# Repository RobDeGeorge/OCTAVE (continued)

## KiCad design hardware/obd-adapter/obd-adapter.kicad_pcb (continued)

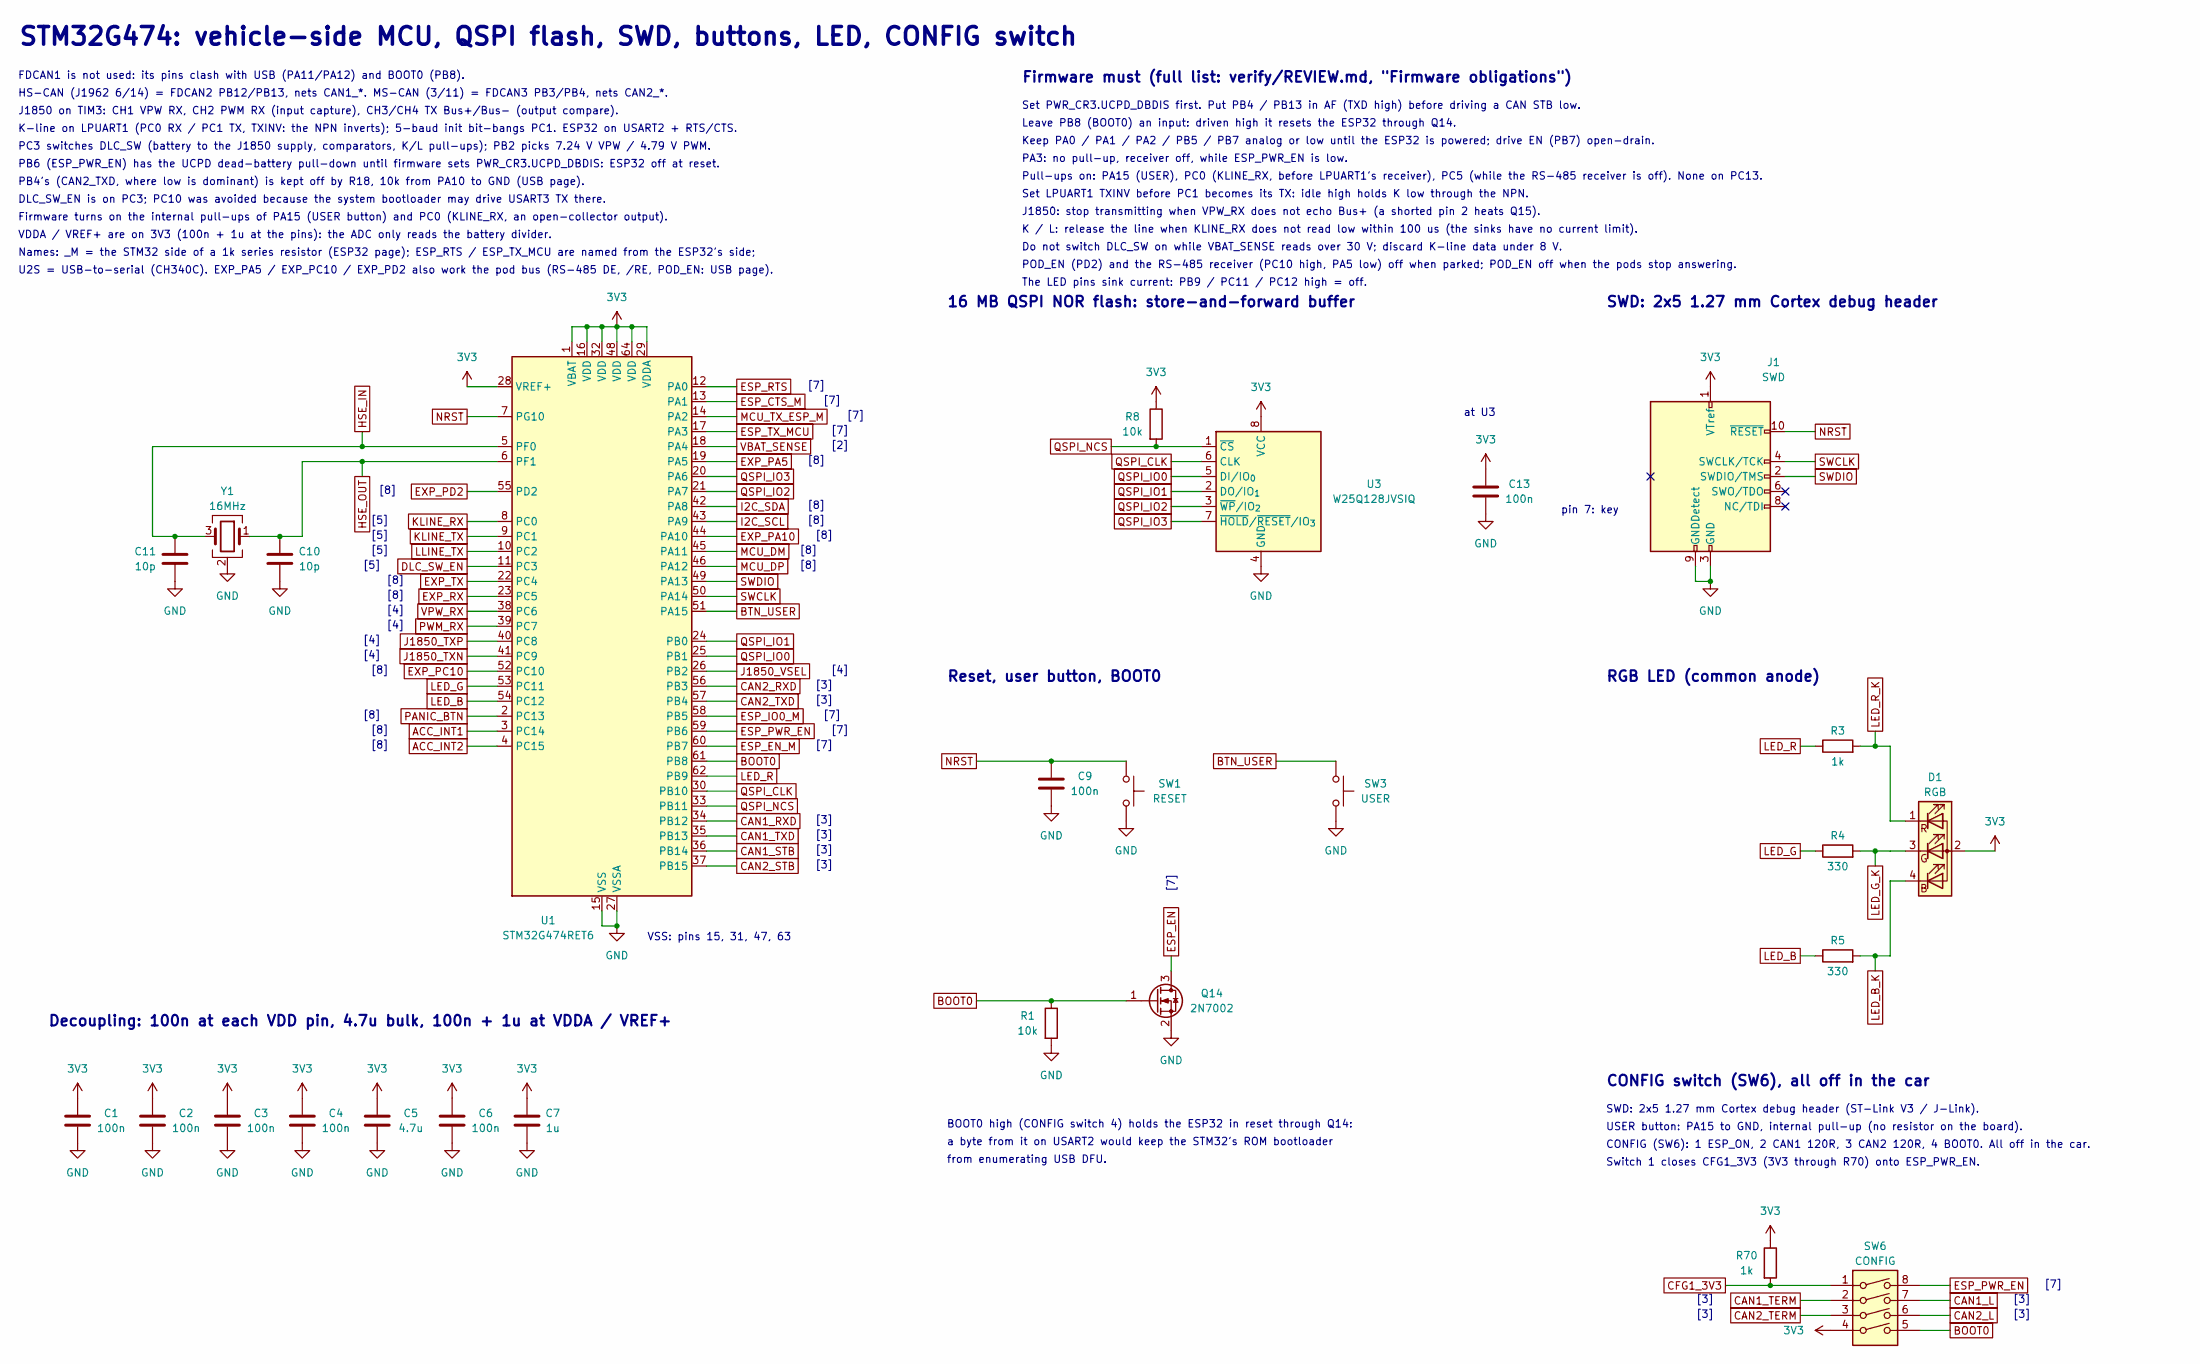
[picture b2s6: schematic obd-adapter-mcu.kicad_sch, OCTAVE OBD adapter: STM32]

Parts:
C1, C2, C3, C4, C6, C9, C13: 100n; C_0402_1005Metric; LCSC C307331
C5: 4.7u; C_0603_1608Metric; LCSC C19666
C7: 1u; C_0402_1005Metric; LCSC C52923
C10, C11: 10p; C_0402_1005Metric; LCSC C32949
D1: RGB; LED_RGB_1615; LCSC C965840
J1: SWD; PinHeader_2x05_P1.27mm_Vertical_SMD; LCSC C41376037
Q14: 2N7002; SOT-23; LCSC C8545
R1, R8: 10k; R_0402_1005Metric; LCSC C25744
R3, R70: 1k; R_0402_1005Metric; LCSC C11702
R4, R5: 330; R_0402_1005Metric; LCSC C25104
SW1: RESET; SW_Push_1P1T_XKB_TS-1187A; LCSC C318884
SW3: USER; SW_Push_1P1T_XKB_TS-1187A; LCSC C318884
SW6: CONFIG; SW_DIP_SPSTx04_Slide_KingTek_DSHP04TS_W7.62mm_P1.27mm; LCSC C40736
U1: STM32G474RET6; LQFP-64_10x10mm_P0.5mm; LCSC C521608
U3: W25Q128JVSIQ; SOIC-8_5.3x5.3mm_P1.27mm; LCSC C97521
Y1: 16MHz; Crystal_SMD_3225-4Pin_3.2x2.5mm; LCSC C13738

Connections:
3V3: C1.1, C2.1, C3.1, C4.1, C5.1, C6.1, C7.1, C13.1, D1.2 (A), J1.1 (VTref), R8.1, R70.1, SW6.4, U1.1 (VBAT), U1.16 (VDD), U1.28 (VREF+), U1.29 (VDDA), U1.32 (VDD), U1.48 (VDD), U1.64 (VDD), U3.8 (VCC); also elsewhere on the board
ACC_INT1: U1.3 (PC14); also elsewhere on the board
ACC_INT2: U1.4 (PC15); also elsewhere on the board
BOOT0: Q14.1 (G), R1.1, SW6.5, U1.61 (PB8)
BTN_USER: SW3.1, U1.51 (PA15)
CAN1_L: SW6.7; also elsewhere on the board
CAN1_RXD: U1.34 (PB12); also elsewhere on the board
CAN1_STB: U1.36 (PB14); also elsewhere on the board
CAN1_TERM: SW6.2; also elsewhere on the board
CAN1_TXD: U1.35 (PB13); also elsewhere on the board
CAN2_L: SW6.6; also elsewhere on the board
CAN2_RXD: U1.56 (PB3); also elsewhere on the board
CAN2_STB: U1.37 (PB15); also elsewhere on the board
CAN2_TERM: SW6.3; also elsewhere on the board
CAN2_TXD: U1.57 (PB4); also elsewhere on the board
CFG1_3V3: R70.2, SW6.1
DLC_SW_EN: U1.11 (PC3); also elsewhere on the board
ESP_CTS_M: U1.13 (PA1); also elsewhere on the board
ESP_EN: Q14.3 (D); also elsewhere on the board
ESP_EN_M: U1.60 (PB7); also elsewhere on the board
ESP_IO0_M: U1.58 (PB5); also elsewhere on the board
ESP_PWR_EN: SW6.8, U1.59 (PB6); also elsewhere on the board
ESP_RTS: U1.12 (PA0); also elsewhere on the board
ESP_TX_MCU: U1.17 (PA3); also elsewhere on the board
EXP_PA5: U1.19 (PA5); also elsewhere on the board
EXP_PA10: U1.44 (PA10); also elsewhere on the board
EXP_PC10: U1.52 (PC10); also elsewhere on the board
EXP_PD2: U1.55 (PD2); also elsewhere on the board
EXP_RX: U1.23 (PC5); also elsewhere on the board
EXP_TX: U1.22 (PC4); also elsewhere on the board
GND: C1.2, C2.2, C3.2, C4.2, C5.2, C6.2, C7.2, C9.2, C10.2, C11.2, C13.2, J1.3 (GND), J1.5 (GND), J1.9 (GNDDetect), Q14.2 (S), R1.2, SW1.2, SW3.2, U1.15 (VSS), U1.27 (VSSA), U1.31 (VSS), U1.47 (VSS), U1.63 (VSS), U3.4 (GND), Y1.2 (G), Y1.4 (G); also elsewhere on the board
HSE_IN: C11.1, U1.5 (PF0), Y1.3
HSE_OUT: C10.1, U1.6 (PF1), Y1.1
I2C_SCL: U1.43 (PA9); also elsewhere on the board
I2C_SDA: U1.42 (PA8); also elsewhere on the board
J1850_TXN: U1.41 (PC9); also elsewhere on the board
J1850_TXP: U1.40 (PC8); also elsewhere on the board
J1850_VSEL: U1.26 (PB2); also elsewhere on the board
KLINE_RX: U1.8 (PC0); also elsewhere on the board
KLINE_TX: U1.9 (PC1); also elsewhere on the board
LED_B: R5.1, U1.54 (PC12)
LED_B_K: D1.4 (BK), R5.2
LED_G: R4.1, U1.53 (PC11)
LED_G_K: D1.3 (GK), R4.2
LED_R: R3.1, U1.62 (PB9)
LED_R_K: D1.1 (RK), R3.2
LLINE_TX: U1.10 (PC2); also elsewhere on the board
MCU_DM: U1.45 (PA11); also elsewhere on the board
MCU_DP: U1.46 (PA12); also elsewhere on the board
MCU_TX_ESP_M: U1.14 (PA2); also elsewhere on the board
NRST: C9.1, J1.10 (~RESET), SW1.1, U1.7 (PG10)
PANIC_BTN: U1.2 (PC13); also elsewhere on the board
PWM_RX: U1.39 (PC7); also elsewhere on the board
QSPI_CLK: U1.30 (PB10), U3.6 (CLK)
QSPI_IO0: U1.25 (PB1), U3.5 (DI/IO_{0})
QSPI_IO1: U1.24 (PB0), U3.2 (DO/IO_{1})
QSPI_IO2: U1.21 (PA7), U3.3 (~WP/IO_{2})
QSPI_IO3: U1.20 (PA6), U3.7 (~HOLD/~RESET/IO_{3})
QSPI_NCS: R8.2, U1.33 (PB11), U3.1 (~CS)
SWCLK: J1.4 (SWCLK/TCK), U1.50 (PA14)
SWDIO: J1.2 (SWDIO/TMS), U1.49 (PA13)
VBAT_SENSE: U1.18 (PA4); also elsewhere on the board
VPW_RX: U1.38 (PC6); also elsewhere on the board

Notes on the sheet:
STM32G474: vehicle-side MCU, QSPI flash, SWD, buttons, LED, CONFIG switch
FDCAN1 is not used: its pins clash with USB (PA11/PA12) and BOOT0 (PB8).
HS-CAN (J1962 6/14) = FDCAN2 PB12/PB13, nets CAN1_*. MS-CAN (3/11) = FDCAN3 PB3/PB4, nets CAN2_*.
J1850 on TIM3: CH1 VPW RX, CH2 PWM RX (input capture), CH3/CH4 TX Bus+/Bus- (output compare).
K-line on LPUART1 (PC0 RX / PC1 TX, TXINV: the NPN inverts); 5-baud init bit-bangs PC1. ESP32 on USART2 + RTS/CTS.
PC3 switches DLC_SW (battery to the J1850 supply, comparators, K/L pull-ups); PB2 picks 7.24 V VPW / 4.79 V PWM.
PB6 (ESP_PWR_EN) has the UCPD dead-battery pull-down until firmware sets PWR_CR3.UCPD_DBDIS: ESP32 off at reset.
PB4's (CAN2_TXD, where low is dominant) is kept off by R18, 10k from PA10 to GND (USB page).
DLC_SW_EN is on PC3; PC10 was avoided because the system bootloader may drive USART3 TX there.
Firmware turns on the internal pull-ups of PA15 (USER button) and PC0 (KLINE_RX, an open-collector output).
VDDA / VREF+ are on 3V3 (100n + 1u at the pins): the ADC only reads the battery divider.
Names: _M = the STM32 side of a 1k series resistor (ESP32 page); ESP_RTS / ESP_TX_MCU are named from the ESP32's side;
U2S = USB-to-serial (CH340C). EXP_PA5 / EXP_PC10 / EXP_PD2 also work the pod bus (RS-485 DE, /RE, POD_EN: USB page).
Firmware must (full list: verify/REVIEW.md, "Firmware obligations")
Set PWR_CR3.UCPD_DBDIS first. Put PB4 / PB13 in AF (TXD high) before driving a CAN STB low.
Leave PB8 (BOOT0) an input: driven high it resets the ESP32 through Q14.
Keep PA0 / PA1 / PA2 / PB5 / PB7 analog or low until the ESP32 is powered; drive EN (PB7) open-drain.
PA3: no pull-up, receiver off, while ESP_PWR_EN is low.
Pull-ups on: PA15 (USER), PC0 (KLINE_RX, before LPUART1's receiver), PC5 (while the RS-485 receiver is off). None on PC13.
Set LPUART1 TXINV before PC1 becomes its TX: idle high holds K low through the NPN.
J1850: stop transmitting when VPW_RX does not echo Bus+ (a shorted pin 2 heats Q15).
K / L: release the line when KLINE_RX does not read low within 100 us (the sinks have no current limit).
Do not switch DLC_SW on while VBAT_SENSE reads over 30 V; discard K-line data under 8 V.
POD_EN (PD2) and the RS-485 receiver (PC10 high, PA5 low) off when parked; POD_EN off when the pods stop answering.
The LED pins sink current: PB9 / PC11 / PC12 high = off.
VSS: pins 15, 31, 47, 63
Decoupling: 100n at each VDD pin, 4.7u bulk, 100n + 1u at VDDA / VREF+
16 MB QSPI NOR flash: store-and-forward buffer
at U3
Reset, user button, BOOT0
BOOT0 high (CONFIG switch 4) holds the ESP32 in reset through Q14:
a byte from it on USART2 would keep the STM32's ROM bootloader
from enumerating USB DFU.
SWD: 2x5 1.27 mm Cortex debug header
pin 7: key
RGB LED (common anode)
CONFIG switch (SW6), all off in the car
SWD: 2x5 1.27 mm Cortex debug header (ST-Link V3 / J-Link).
USER button: PA15 to GND, internal pull-up (no resistor on the board).
CONFIG (SW6): 1 ESP_ON, 2 CAN1 120R, 3 CAN2 120R, 4 BOOT0. All off in the car.

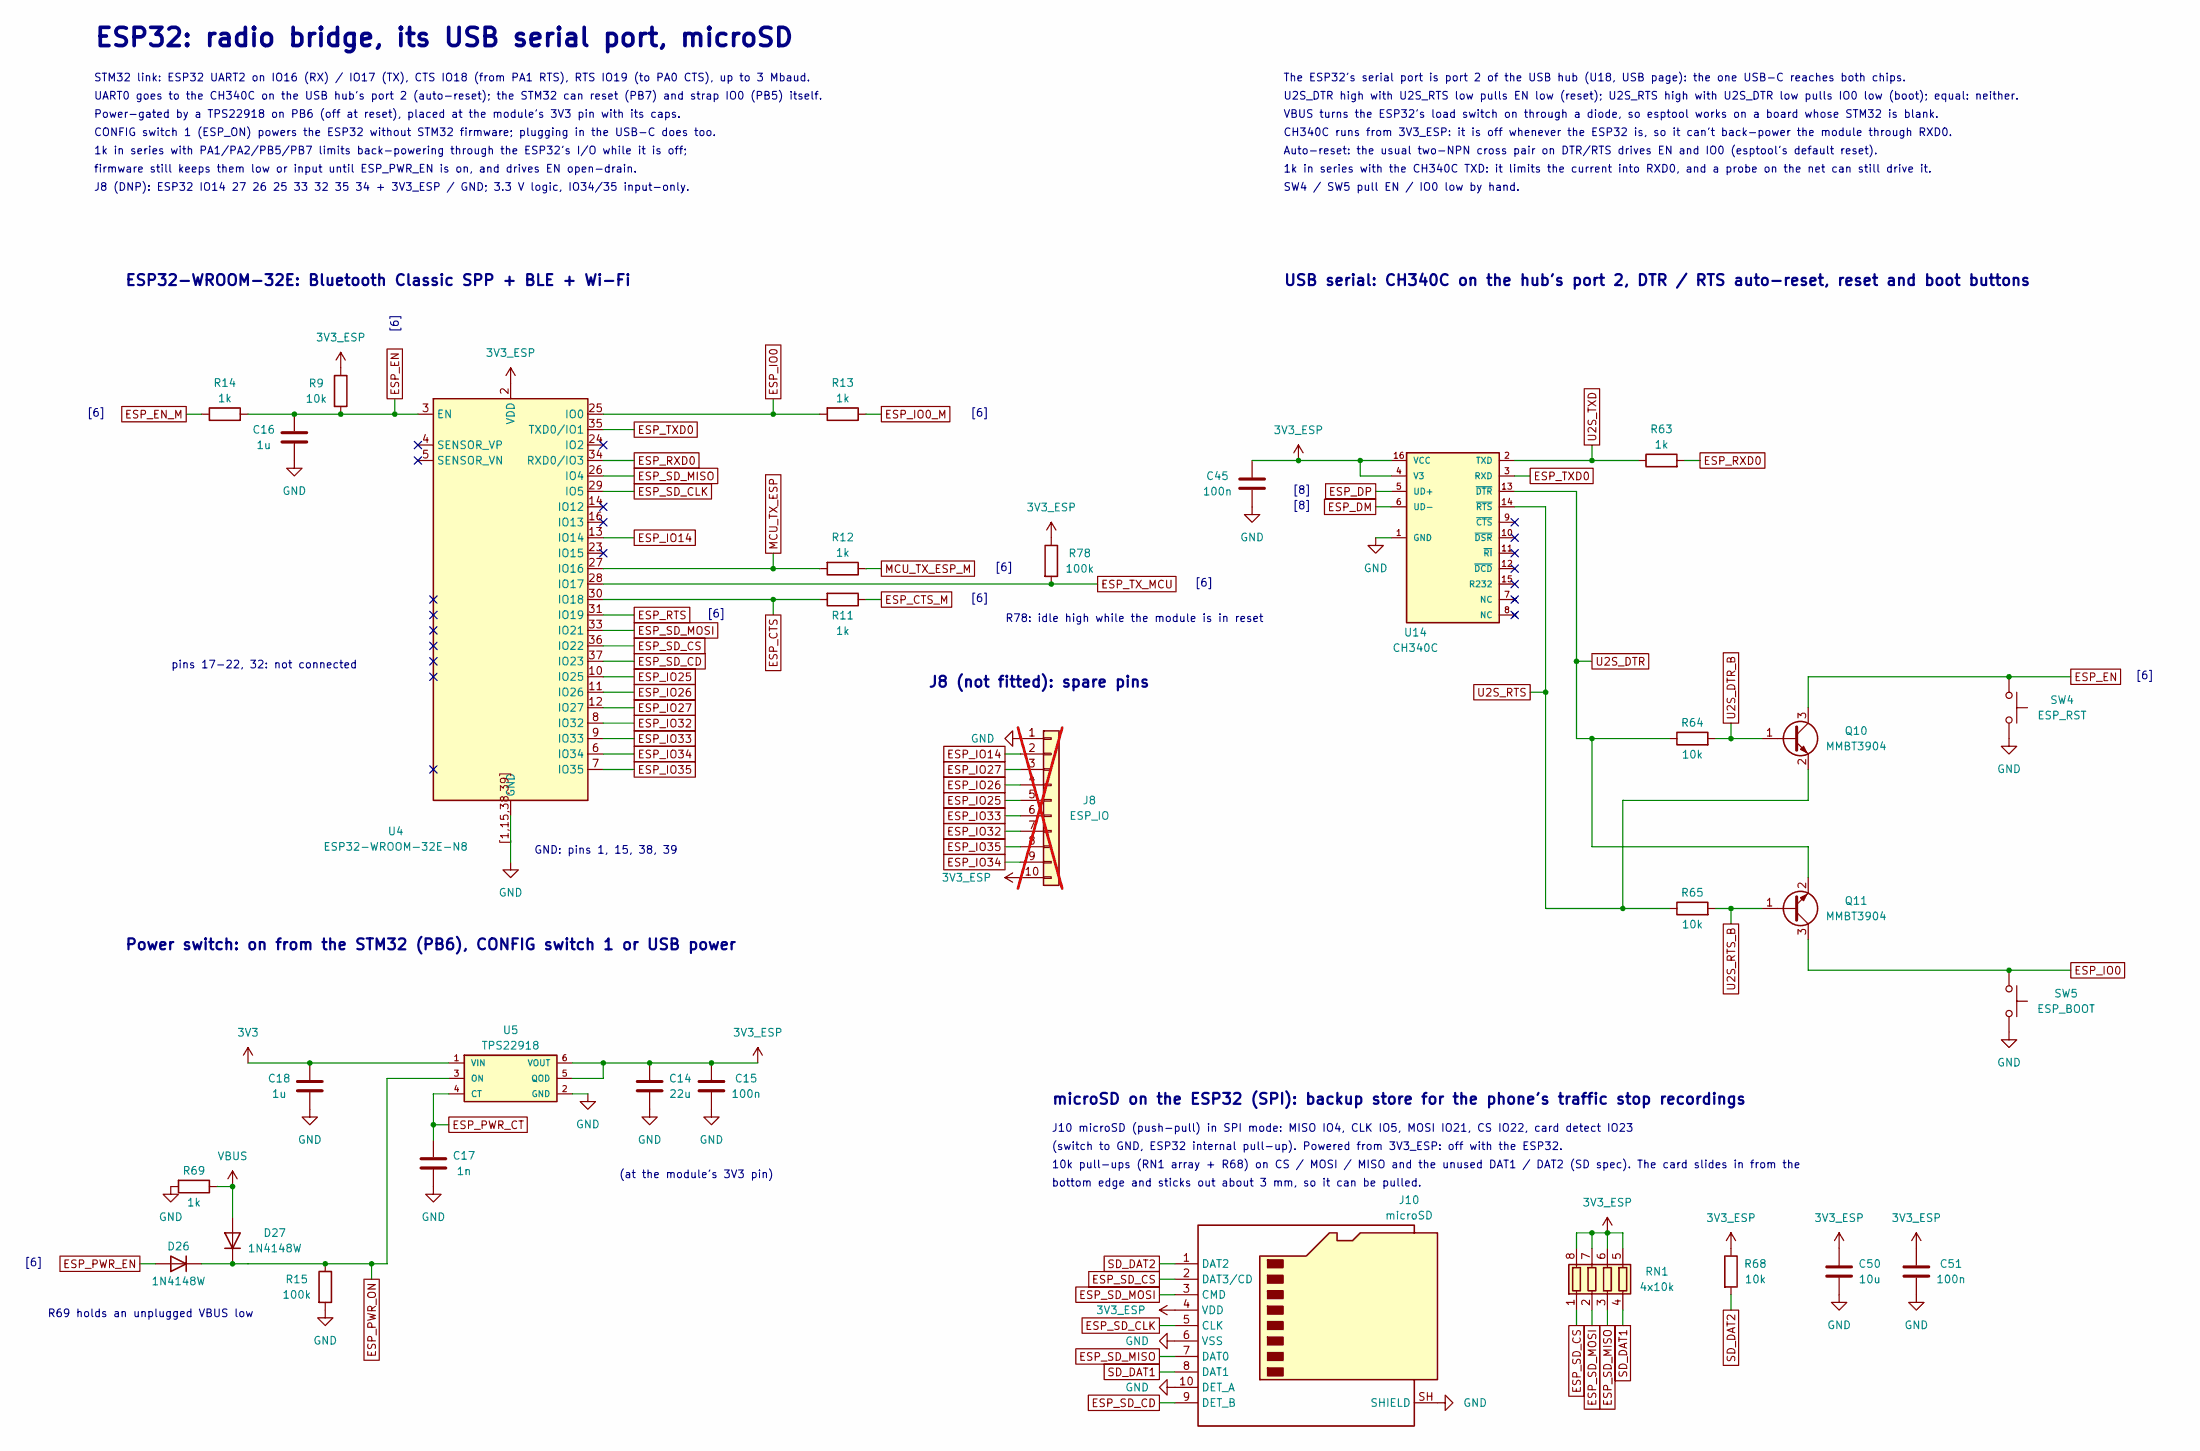
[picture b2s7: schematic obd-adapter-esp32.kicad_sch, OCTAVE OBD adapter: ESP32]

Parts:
C14: 22u; C_1206_3216Metric; LCSC C12891
C15, C45, C51: 100n; C_0402_1005Metric; LCSC C307331
C16, C18: 1u; C_0402_1005Metric; LCSC C52923
C17: 1n; C_0402_1005Metric; LCSC C1523
C50: 10u; C_0603_1608Metric; LCSC C96446
D26, D27: 1N4148W; D_SOD-123; LCSC C81598
J8: ESP_IO; PinHeader_1x10_P2.54mm_Vertical; not fitted
J10: microSD; microSD_HC_Molex_104031-0811; LCSC C585350
Q10, Q11: MMBT3904; SOT-23; LCSC C20526
R9, R64, R65, R68: 10k; R_0402_1005Metric; LCSC C25744
R11, R12, R13, R14, R63: 1k; R_0402_1005Metric; LCSC C11702
R15, R78: 100k; R_0402_1005Metric; LCSC C25741
R69: 1k; R_0603_1608Metric; LCSC C21190
RN1: 4x10k; R_Array_Convex_4x0603; LCSC C29718
SW4: ESP_RST; SW_Push_1P1T_XKB_TS-1187A; LCSC C318884
SW5: ESP_BOOT; SW_Push_1P1T_XKB_TS-1187A; LCSC C318884
U4: ESP32-WROOM-32E-N8; ESP32-WROOM-32E; LCSC C701342
U5: TPS22918; SOT-23-6; LCSC C131941
U14: CH340C; SOIC-16_3.9x9.9mm_P1.27mm; LCSC C84681

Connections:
3V3: C18.1, U5.1 (VIN); also elsewhere on the board
3V3_ESP: C14.1, C15.1, C45.1, C50.1, C51.1, J8.10, J10.4 (VDD), R9.1, R68.1, R78.1, RN1.5 (R4.2), RN1.6 (R3.2), RN1.7 (R2.2), RN1.8 (R1.2), U4.2 (VDD), U5.5 (QOD), U5.6 (VOUT), U14.4 (V3), U14.16 (VCC)
ESP_CTS: R11.2, U4.30 (IO18)
ESP_CTS_M: R11.1; also elsewhere on the board
ESP_DM: U14.6 (UD-); also elsewhere on the board
ESP_DP: U14.5 (UD+); also elsewhere on the board
ESP_EN: C16.1, Q10.3 (C), R9.2, R14.2, SW4.1, U4.3 (EN); also elsewhere on the board
ESP_EN_M: R14.1; also elsewhere on the board
ESP_IO0: Q11.3 (C), R13.2, SW5.1, U4.25 (IO0)
ESP_IO0_M: R13.1; also elsewhere on the board
ESP_IO14: J8.2, U4.13 (IO14)
ESP_IO25: J8.5, U4.10 (IO25)
ESP_IO26: J8.4, U4.11 (IO26)
ESP_IO27: J8.3, U4.12 (IO27)
ESP_IO32: J8.7, U4.8 (IO32)
ESP_IO33: J8.6, U4.9 (IO33)
ESP_IO34: J8.9, U4.6 (IO34)
ESP_IO35: J8.8, U4.7 (IO35)
ESP_PWR_CT: C17.1, U5.4 (CT)
ESP_PWR_EN: D26.2 (A); also elsewhere on the board
ESP_PWR_ON: D26.1 (K), D27.1 (K), R15.1, U5.3 (ON)
ESP_RTS: U4.31 (IO19); also elsewhere on the board
ESP_RXD0: R63.2, U4.34 (RXD0/IO3)
ESP_SD_CD: J10.9 (DET_B), U4.37 (IO23)
ESP_SD_CLK: J10.5 (CLK), U4.29 (IO5)
ESP_SD_CS: J10.2 (DAT3/CD), RN1.1 (R1.1), U4.36 (IO22)
ESP_SD_MISO: J10.7 (DAT0), RN1.3 (R3.1), U4.26 (IO4)
ESP_SD_MOSI: J10.3 (CMD), RN1.2 (R2.1), U4.33 (IO21)
ESP_TXD0: U4.35 (TXD0/IO1), U14.3 (RXD)
ESP_TX_MCU: R78.2, U4.28 (IO17); also elsewhere on the board
GND: C14.2, C15.2, C16.2, C17.2, C18.2, C45.2, C50.2, C51.2, J8.1, J10.6 (VSS), J10.10 (DET_A), J10.SH (SHIELD), R15.2, R69.2, SW4.2, SW5.2, U4.1, U4.15, U4.38, U4.39, U4.[1,15,38,39] (GND), U5.2 (GND), U14.1 (GND); also elsewhere on the board
MCU_TX_ESP: R12.2, U4.27 (IO16)
MCU_TX_ESP_M: R12.1; also elsewhere on the board
SD_DAT1: J10.8 (DAT1), RN1.4 (R4.1)
SD_DAT2: J10.1 (DAT2), R68.2
U2S_DTR: Q11.2 (E), R64.1, U14.13 (~DTR)
U2S_DTR_B: Q10.1 (B), R64.2
U2S_RTS: Q10.2 (E), R65.1, U14.14 (~RTS)
U2S_RTS_B: Q11.1 (B), R65.2
U2S_TXD: R63.1, U14.2 (TXD)
VBUS: D27.2 (A), R69.1; also elsewhere on the board

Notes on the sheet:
ESP32: radio bridge, its USB serial port, microSD
STM32 link: ESP32 UART2 on IO16 (RX) / IO17 (TX), CTS IO18 (from PA1 RTS), RTS IO19 (to PA0 CTS), up to 3 Mbaud.
UART0 goes to the CH340C on the USB hub's port 2 (auto-reset); the STM32 can reset (PB7) and strap IO0 (PB5) itself.
Power-gated by a TPS22918 on PB6 (off at reset), placed at the module's 3V3 pin with its caps.
CONFIG switch 1 (ESP_ON) powers the ESP32 without STM32 firmware; plugging in the USB-C does too.
1k in series with PA1/PA2/PB5/PB7 limits back-powering through the ESP32's I/O while it is off;
firmware still keeps them low or input until ESP_PWR_EN is on, and drives EN open-drain.
J8 (DNP): ESP32 IO14 27 26 25 33 32 35 34 + 3V3_ESP / GND; 3.3 V logic, IO34/35 input-only.
The ESP32's serial port is port 2 of the USB hub (U18, USB page): the one USB-C reaches both chips.
U2S_DTR high with U2S_RTS low pulls EN low (reset); U2S_RTS high with U2S_DTR low pulls IO0 low (boot); equal: neither.
VBUS turns the ESP32's load switch on through a diode, so esptool works on a board whose STM32 is blank.
CH340C runs from 3V3_ESP: it is off whenever the ESP32 is, so it can't back-power the module through RXD0.
Auto-reset: the usual two-NPN cross pair on DTR/RTS drives EN and IO0 (esptool's default reset).
1k in series with the CH340C TXD: it limits the current into RXD0, and a probe on the net can still drive it.
SW4 / SW5 pull EN / IO0 low by hand.
ESP32-WROOM-32E: Bluetooth Classic SPP + BLE + Wi-Fi
pins 17-22, 32: not connected
GND: pins 1, 15, 38, 39
R78: idle high while the module is in reset
J8 (not fitted): spare pins
Power switch: on from the STM32 (PB6), CONFIG switch 1 or USB power
R69 holds an unplugged VBUS low
(at the module's 3V3 pin)
USB serial: CH340C on the hub's port 2, DTR / RTS auto-reset, reset and boot buttons
microSD on the ESP32 (SPI): backup store for the phone's traffic stop recordings
J10 microSD (push-pull) in SPI mode: MISO IO4, CLK IO5, MOSI IO21, CS IO22, card detect IO23
(switch to GND, ESP32 internal pull-up). Powered from 3V3_ESP: off with the ESP32.
10k pull-ups (RN1 array + R68) on CS / MOSI / MISO and the unused DAT1 / DAT2 (SD spec). The card slides in from the
bottom edge and sticks out about 3 mm, so it can be pulled.
[6]
[8]

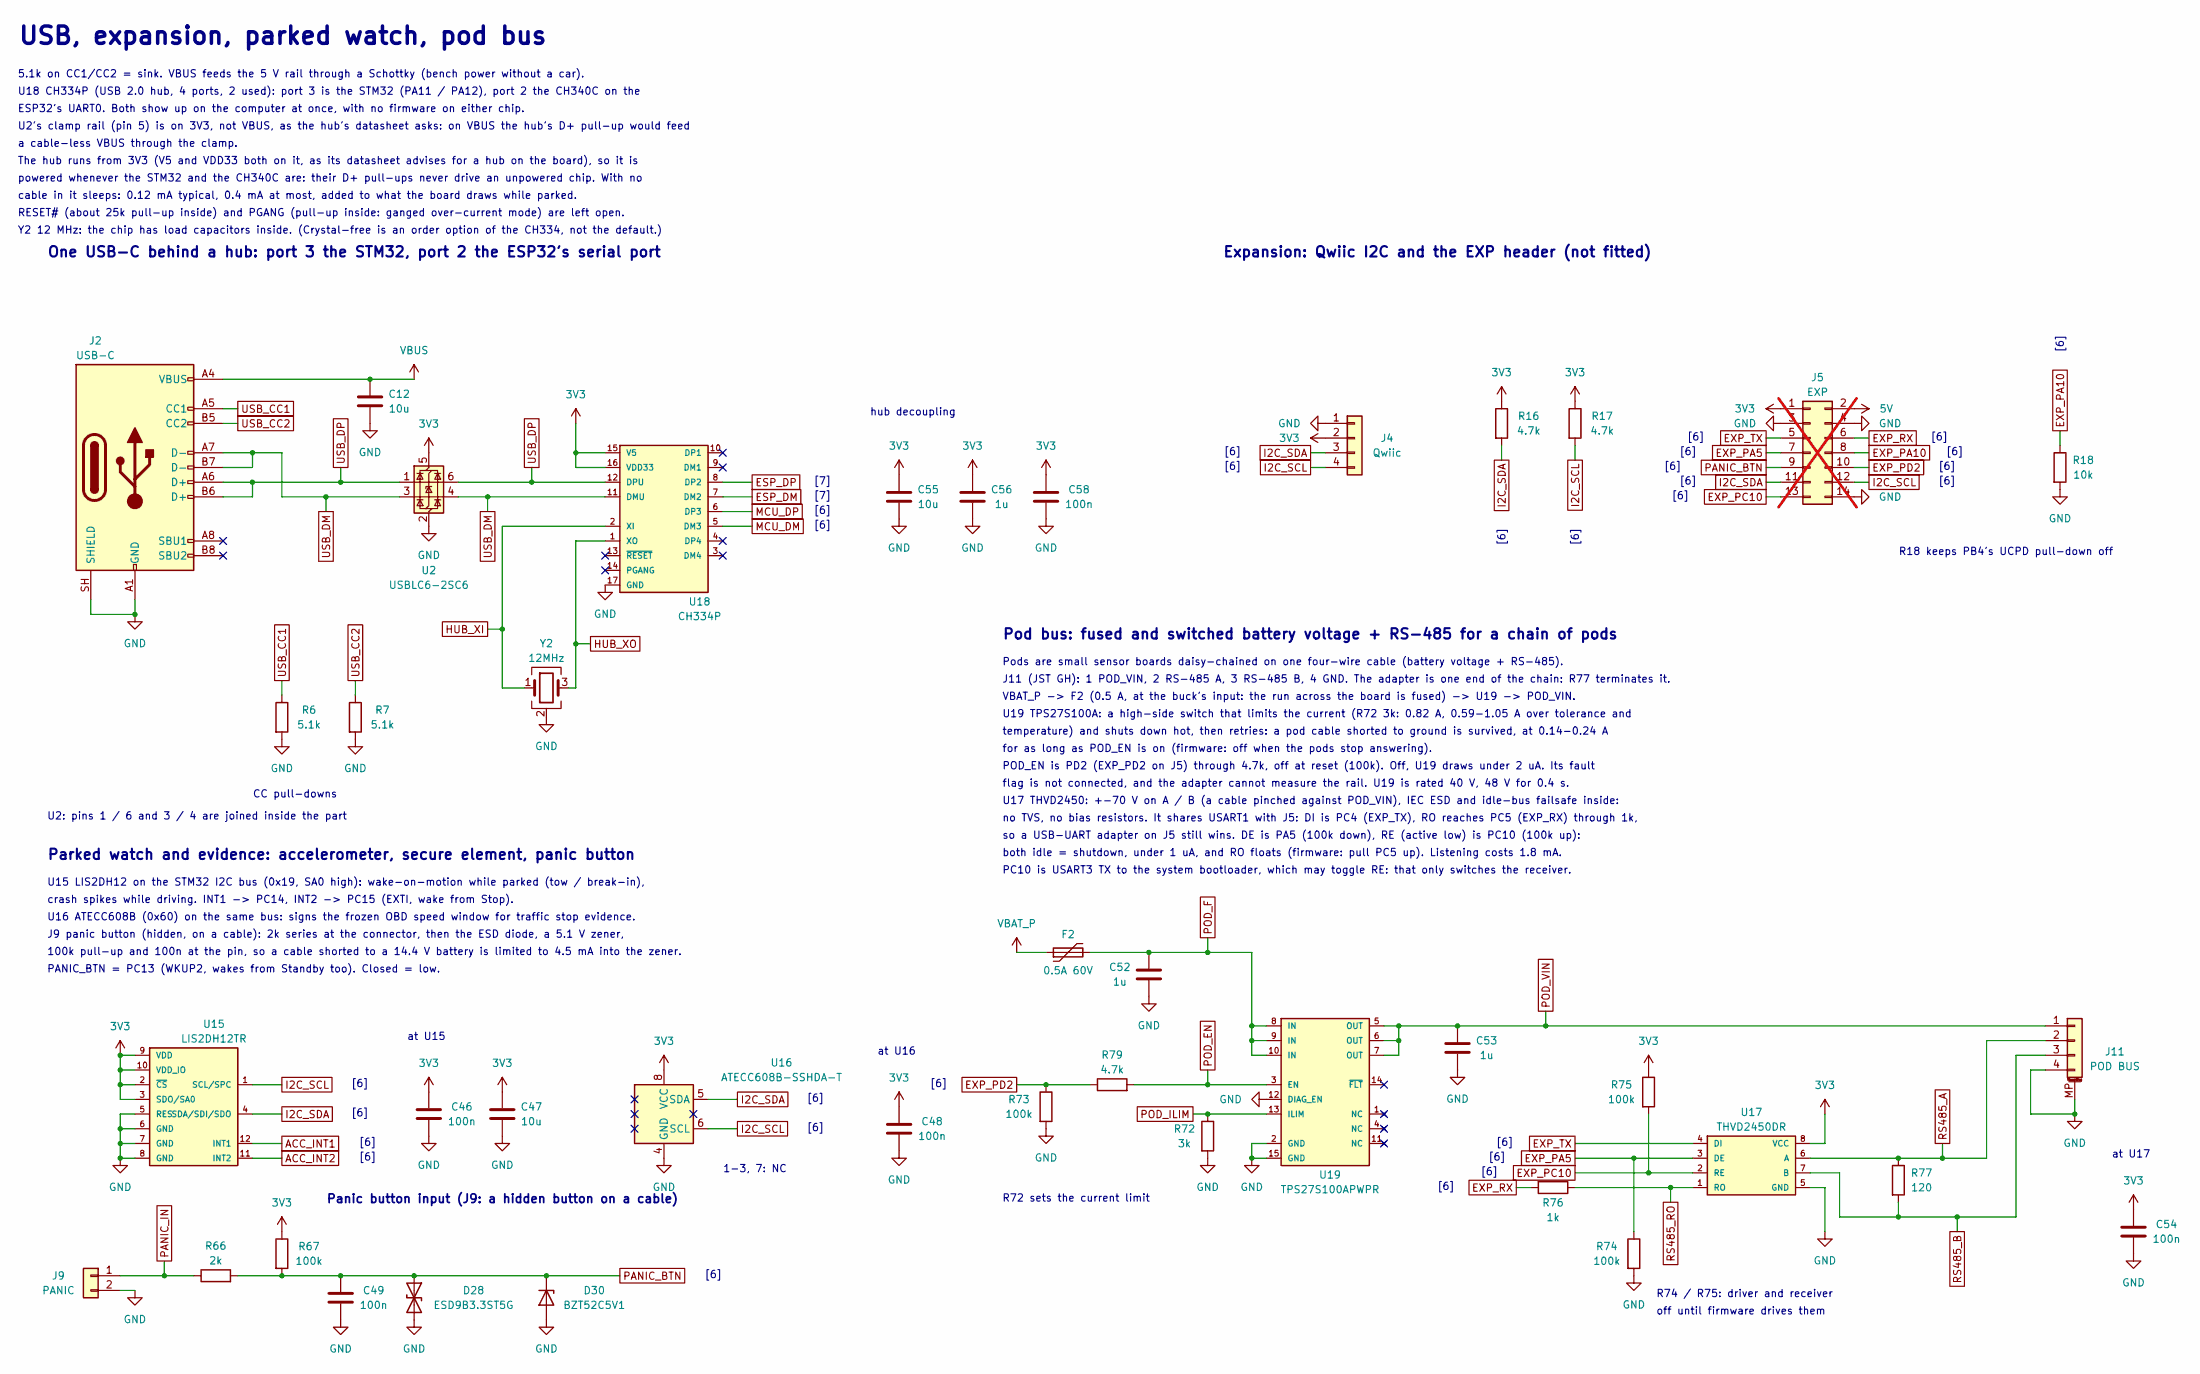
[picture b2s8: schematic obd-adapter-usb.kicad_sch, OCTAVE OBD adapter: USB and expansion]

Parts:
C12, C47, C55: 10u; C_0603_1608Metric; LCSC C96446
C46, C48, C49, C54, C58: 100n; C_0402_1005Metric; LCSC C307331
C52, C53: 1u; C_0603_1608Metric; LCSC C15849
C56: 1u; C_0402_1005Metric; LCSC C52923
D28: ESD9B3.3ST5G; D_SOD-923; LCSC C96512
D30: BZT52C5V1; D_SOD-123; LCSC C19077401
F2: 0.5A 60V; Fuse_1812_4532Metric; LCSC C19078719
J2: USB-C; USB_C_Receptacle_HRO_TYPE-C-31-M-12; LCSC C165948
J4: Qwiic; JST_SH_SM04B-SRSS-TB_1x04-1MP_P1.00mm_Horizontal; LCSC C160404
J5: EXP; PinHeader_2x07_P2.54mm_Vertical; not fitted
J9: PANIC; JST_SH_SM02B-SRSS-TB_1x02-1MP_P1.00mm_Horizontal; LCSC C160402
J11: POD BUS; JST_GH_SM04B-GHS-TB_1x04-1MP_P1.25mm_Horizontal; LCSC C189895
R6, R7: 5.1k; R_0402_1005Metric; LCSC C25905
R16, R17, R79: 4.7k; R_0402_1005Metric; LCSC C25900
R18: 10k; R_0402_1005Metric; LCSC C25744
R66: 2k; R_1206_3216Metric; LCSC C17944
R67, R73, R74, R75: 100k; R_0402_1005Metric; LCSC C25741
R72: 3k; R_0603_1608Metric; LCSC C4211
R76: 1k; R_0402_1005Metric; LCSC C11702
R77: 120; R_1206_3216Metric; LCSC C17909
U2: USBLC6-2SC6; SOT-23-6; LCSC C2687116
U15: LIS2DH12TR; LGA-12_2x2mm_P0.5mm; LCSC C110926
U16: ATECC608B-SSHDA-T; SOIC-8_3.9x4.9mm_P1.27mm; LCSC C1518769
U17: THVD2450DR; SOIC-8_3.9x4.9mm_P1.27mm; LCSC C2672621
U18: CH334P; WCH_QFN-16-1EP_3x3mm_P0.5mm_EP1.8x1.8mm; LCSC C5373042
U19: TPS27S100APWPR; Texas_HTSSOP-14-1EP_4.4x5mm_P0.65mm_EP3.4x5mm_Mask2.94x3.34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; LCSC C2879389
Y2: 12MHz; Crystal_SMD_3225-4Pin_3.2x2.5mm; LCSC C9002

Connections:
3V3: C46.1, C47.1, C48.1, C54.1, C55.1, C56.1, C58.1, J4.2, J5.1, R16.1, R17.1, R67.1, R75.1, U2.5 (VBUS), U15.2 (~CS), U15.3 (SDO/SA0), U15.9 (VDD), U15.10 (VDD_IO), U16.8 (VCC), U17.8 (VCC), U18.15 (V5), U18.16 (VDD33); also elsewhere on the board
5V: J5.2; also elsewhere on the board
ACC_INT1: U15.12 (INT1); also elsewhere on the board
ACC_INT2: U15.11 (INT2); also elsewhere on the board
ESP_DM: U18.7 (DM2); also elsewhere on the board
ESP_DP: U18.8 (DP2); also elsewhere on the board
EXP_PA5: J5.7, R74.1, U17.3 (DE); also elsewhere on the board
EXP_PA10: J5.8, R18.1; also elsewhere on the board
EXP_PC10: J5.13, R75.2, U17.2 (RE); also elsewhere on the board
EXP_PD2: J5.10, R73.1, R79.1; also elsewhere on the board
EXP_RX: J5.6, R76.2; also elsewhere on the board
EXP_TX: J5.5, U17.4 (DI); also elsewhere on the board
GND: C12.2, C46.2, C47.2, C48.2, C49.2, C52.2, C53.2, C54.2, C55.2, C56.2, C58.2, D28.2 (A2), D30.2 (A), J2.A1 (GND), J2.A12 (GND), J2.B1 (GND), J2.B12 (GND), J2.SH (SHIELD), J4.1, J5.3, J5.4, J5.14, J9.2, J11.4, J11.MP (MountPin), R6.2, R7.2, R18.2, R72.2, R73.2, R74.2, U2.2 (GND), U15.5 (RES), U15.6 (GND), U15.7 (GND), U15.8 (GND), U16.4 (GND), U17.5 (GND), U18.17 (GND), U19.2 (GND), U19.12 (DIAG_EN), U19.15 (GND), Y2.2 (G), Y2.4 (G); also elsewhere on the board
HUB_XI: U18.2 (XI), Y2.1
HUB_XO: U18.1 (XO), Y2.3
I2C_SCL: J4.4, J5.12, R17.2, U15.1 (SCL/SPC), U16.6 (SCL); also elsewhere on the board
I2C_SDA: J4.3, J5.11, R16.2, U15.4 (SDA/SDI/SDO), U16.5 (SDA); also elsewhere on the board
MCU_DM: U18.5 (DM3); also elsewhere on the board
MCU_DP: U18.6 (DP3); also elsewhere on the board
PANIC_BTN: C49.1, D28.1 (A1), D30.1 (K), J5.9, R66.2, R67.2; also elsewhere on the board
PANIC_IN: J9.1, R66.1
POD_EN: R79.2, U19.3 (EN)
POD_F: C52.1, F2.2, U19.8 (IN), U19.9 (IN), U19.10 (IN)
POD_ILIM: R72.1, U19.13 (ILIM)
POD_VIN: C53.1, J11.1, U19.5 (OUT), U19.6 (OUT), U19.7 (OUT)
RS485_A: J11.2, R77.1, U17.6 (A)
RS485_B: J11.3, R77.2, U17.7 (B)
RS485_RO: R76.1, U17.1 (RO)
USB_CC1: J2.A5 (CC1), R6.1
USB_CC2: J2.B5 (CC2), R7.1
USB_DM: J2.A7 (D-), J2.B7 (D-), U2.3 (I/O2), U2.4 (I/O2), U18.11 (DMU)
USB_DP: J2.A6 (D+), J2.B6 (D+), U2.1 (I/O1), U2.6 (I/O1), U18.12 (DPU)
VBAT_P: F2.1; also elsewhere on the board
VBUS: C12.1, J2.A4 (VBUS), J2.A9 (VBUS), J2.B4 (VBUS), J2.B9 (VBUS); also elsewhere on the board

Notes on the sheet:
USB, expansion, parked watch, pod bus
5.1k on CC1/CC2 = sink. VBUS feeds the 5 V rail through a Schottky (bench power without a car).
U18 CH334P (USB 2.0 hub, 4 ports, 2 used): port 3 is the STM32 (PA11 / PA12), port 2 the CH340C on the
ESP32's UART0. Both show up on the computer at once, with no firmware on either chip.
U2's clamp rail (pin 5) is on 3V3, not VBUS, as the hub's datasheet asks: on VBUS the hub's D+ pull-up would feed
a cable-less VBUS through the clamp.
The hub runs from 3V3 (V5 and VDD33 both on it, as its datasheet advises for a hub on the board), so it is
powered whenever the STM32 and the CH340C are: their D+ pull-ups never drive an unpowered chip. With no
cable in it sleeps: 0.12 mA typical, 0.4 mA at most, added to what the board draws while parked.
RESET# (about 25k pull-up inside) and PGANG (pull-up inside: ganged over-current mode) are left open.
Y2 12 MHz: the chip has load capacitors inside. (Crystal-free is an order option of the CH334, not the default.)
One USB-C behind a hub: port 3 the STM32, port 2 the ESP32's serial port
U2: pins 1 / 6 and 3 / 4 are joined inside the part
CC pull-downs
hub decoupling
Expansion: Qwiic I2C and the EXP header (not fitted)
R18 keeps PB4's UCPD pull-down off
Parked watch and evidence: accelerometer, secure element, panic button
U15 LIS2DH12 on the STM32 I2C bus (0x19, SA0 high): wake-on-motion while parked (tow / break-in),
crash spikes while driving. INT1 -> PC14, INT2 -> PC15 (EXTI, wake from Stop).
U16 ATECC608B (0x60) on the same bus: signs the frozen OBD speed window for traffic stop evidence.
J9 panic button (hidden, on a cable): 2k series at the connector, then the ESD diode, a 5.1 V zener,
100k pull-up and 100n at the pin, so a cable shorted to a 14.4 V battery is limited to 4.5 mA into the zener.
PANIC_BTN = PC13 (WKUP2, wakes from Standby too). Closed = low.
at U15
at U16
1-3, 7: NC
Panic button input (J9: a hidden button on a cable)
Pod bus: fused and switched battery voltage + RS-485 for a chain of pods
Pods are small sensor boards daisy-chained on one four-wire cable (battery voltage + RS-485).
J11 (JST GH): 1 POD_VIN, 2 RS-485 A, 3 RS-485 B, 4 GND. The adapter is one end of the chain: R77 terminates it.
VBAT_P -> F2 (0.5 A, at the buck's input: the run across the board is fused) -> U19 -> POD_VIN.
U19 TPS27S100A: a high-side switch that limits the current (R72 3k: 0.82 A, 0.59-1.05 A over tolerance and
temperature) and shuts down hot, then retries: a pod cable shorted to ground is survived, at 0.14-0.24 A
for as long as POD_EN is on (firmware: off when the pods stop answering).
POD_EN is PD2 (EXP_PD2 on J5) through 4.7k, off at reset (100k). Off, U19 draws under 2 uA. Its fault
flag is not connected, and the adapter cannot measure the rail. U19 is rated 40 V, 48 V for 0.4 s.
U17 THVD2450: +-70 V on A / B (a cable pinched against POD_VIN), IEC ESD and idle-bus failsafe inside:
no TVS, no bias resistors. It shares USART1 with J5: DI is PC4 (EXP_TX), RO reaches PC5 (EXP_RX) through 1k,
so a USB-UART adapter on J5 still wins. DE is PA5 (100k down), RE (active low) is PC10 (100k up):
